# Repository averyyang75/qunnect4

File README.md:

# Qunnect4

---

Qunnect4 is designed as an educational board game rooted in the principles of quantum mechanics. With using simulated bichromatic photons, it illustrates the counterintuitive aspects of quantum phenomena and explains fundamental concepts such as superposition, collapse, and entanglement. By encapsulating quantum physics within a physical board game format, Qunnect4 bridges the mysterious realm of quantum physics with the classical world, providing a straightforward, interactive and hands-on experience.

## Construction of Apparatus

Qunnect4 consists of 42 tokens and 1 game board.

Each token is made with a PCB, assembled with one blue and one red LED, two resistors, four diodes, one radio transmitter and one receiver, four push buttons, and one battery holder. Powered by a battery, a token simulates a bichromatic photon. The token is superposed when turned on initially, emitting both blue and red LEDs. When a red or blue button is pushed, the token collapses, emitting only one LED.

The 42 tokens are grouped into 21 pairs. Each pair of tokens simulate a pair of “entangled photons”, with using the paired radio modules. Measuring one token will collapse both tokens simultaneously (one red and one blue).

The game board can be made with wood or foam board.

## Use of Apparatus

As a quantum adaptation of the popular game Connect 4, Qunnect4 is designed to provide hands-on experiences that help players quickly learn key quantum concepts such as superposition, collapse, and entanglement with ease.

Players are encouraged to use the apparatus in a manner like playing Connect 4, with following differences:

- In classic Connect 4, each player places 1 token each turn.
- In Qunnect 4, each player places a pair of entangled tokens each turn.
- A player may choose not to place tokens. Instead, the player can press a button to
collapse a pair of entangled tokens on board.
- To prevent a cycling condition, where one player always collapses the tokens placed by
the other, a player is not allowed to collapse a token unless its row or column is fully occupied. This rule ensures a fair and balanced gameplay experience for both players.

## Related Projects

[Qunnect4 Web](https://github.com/averyyang75/qunnect4-web) implements Qunnect4 in the web application format, offering cost-free accessibility and improved availability.

[Qunnect4 Web game](https://qunnect4.app) is online now.

&copy; Avery Yang

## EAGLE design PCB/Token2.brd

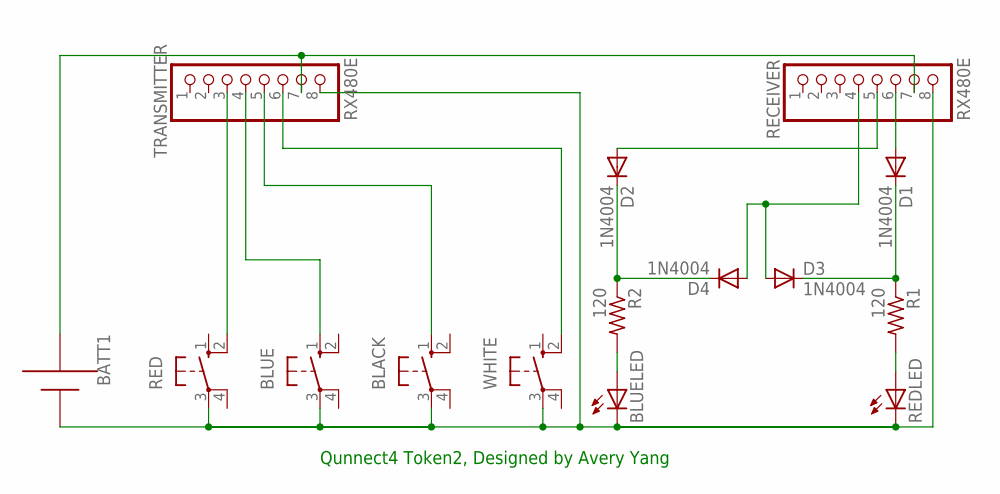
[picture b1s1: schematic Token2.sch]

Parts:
BATT1: AAA; 12BH412
BLACK: 10-XX; B3F-10XX
BLUE: 10-XX; B3F-10XX
BLUELED: LED5MM
D1, D2, D3, D4: 1N4004; DO41-10
R1, R2: 120; 0207/10
RECEIVER: RX480E; 1X08
RED: 10-XX; B3F-10XX
REDLED: LED5MM
TRANSMITTER: RX480E; 1X08
WHITE: 10-XX; B3F-10XX

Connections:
unnamed: BATT1.+, BLACK.3, BLUE.3, BLUELED.K (C), RECEIVER.8, RED.3, REDLED.K (C), TRANSMITTER.8, WHITE.3
unnamed: D2.C, D4.C, R2.1
unnamed: TRANSMITTER.6, WHITE.2 (S1)
unnamed: BLUE.1 (S), TRANSMITTER.4
unnamed: RED.2 (S1), TRANSMITTER.3
unnamed: BLACK.1 (S), TRANSMITTER.5
unnamed: D2.A, RECEIVER.5
unnamed: D1.A, RECEIVER.6
unnamed: D1.C, D3.C, R1.1
unnamed: R1.2, REDLED.A
unnamed: BLUELED.A, R2.2
unnamed: D3.A, D4.A, RECEIVER.4
unnamed: BATT1.-, RECEIVER.7, TRANSMITTER.7

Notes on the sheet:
Qunnect4 Token2, Designed by Avery Yang

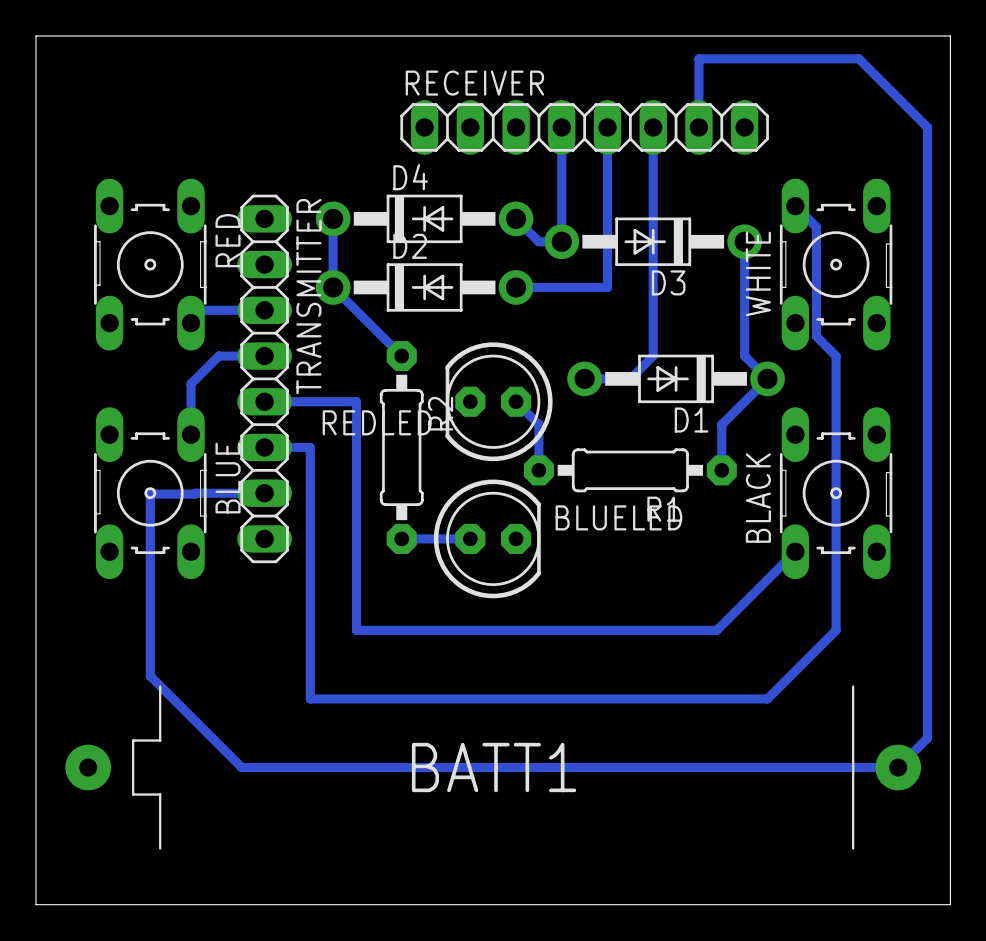
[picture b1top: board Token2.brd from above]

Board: 2 copper layers, 50.8 x 48.3 mm, 15 parts (0 on the bottom side), 13 nets.
